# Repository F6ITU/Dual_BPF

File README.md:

# Alexiares dual BPF for Orion/Anvelina SDR Board

1 to 60 MHz Band pass filter for dual ADC SDR  (Orion class, Anvelina, Red Pitaya)

This pcb serves as RX bandpass for the new generation of Alexiares frontend

It replace the former Alexiares HPF filter and uses the very same SPI bus protocol

Please note that on BPF1  

K23, FB45, FB46, R11, R12, C106 and C93 should NOT be soldered

 (pads 3-10 and 9-4 should be strapped)
 
Signal RX2_GND is not used

BPF2 should be fully assembled, with K23, FB45, FB46, R11, R12, C106 and C93. Signal RX2_GND should be present on J6

(see Alexandrie V2 wirering )

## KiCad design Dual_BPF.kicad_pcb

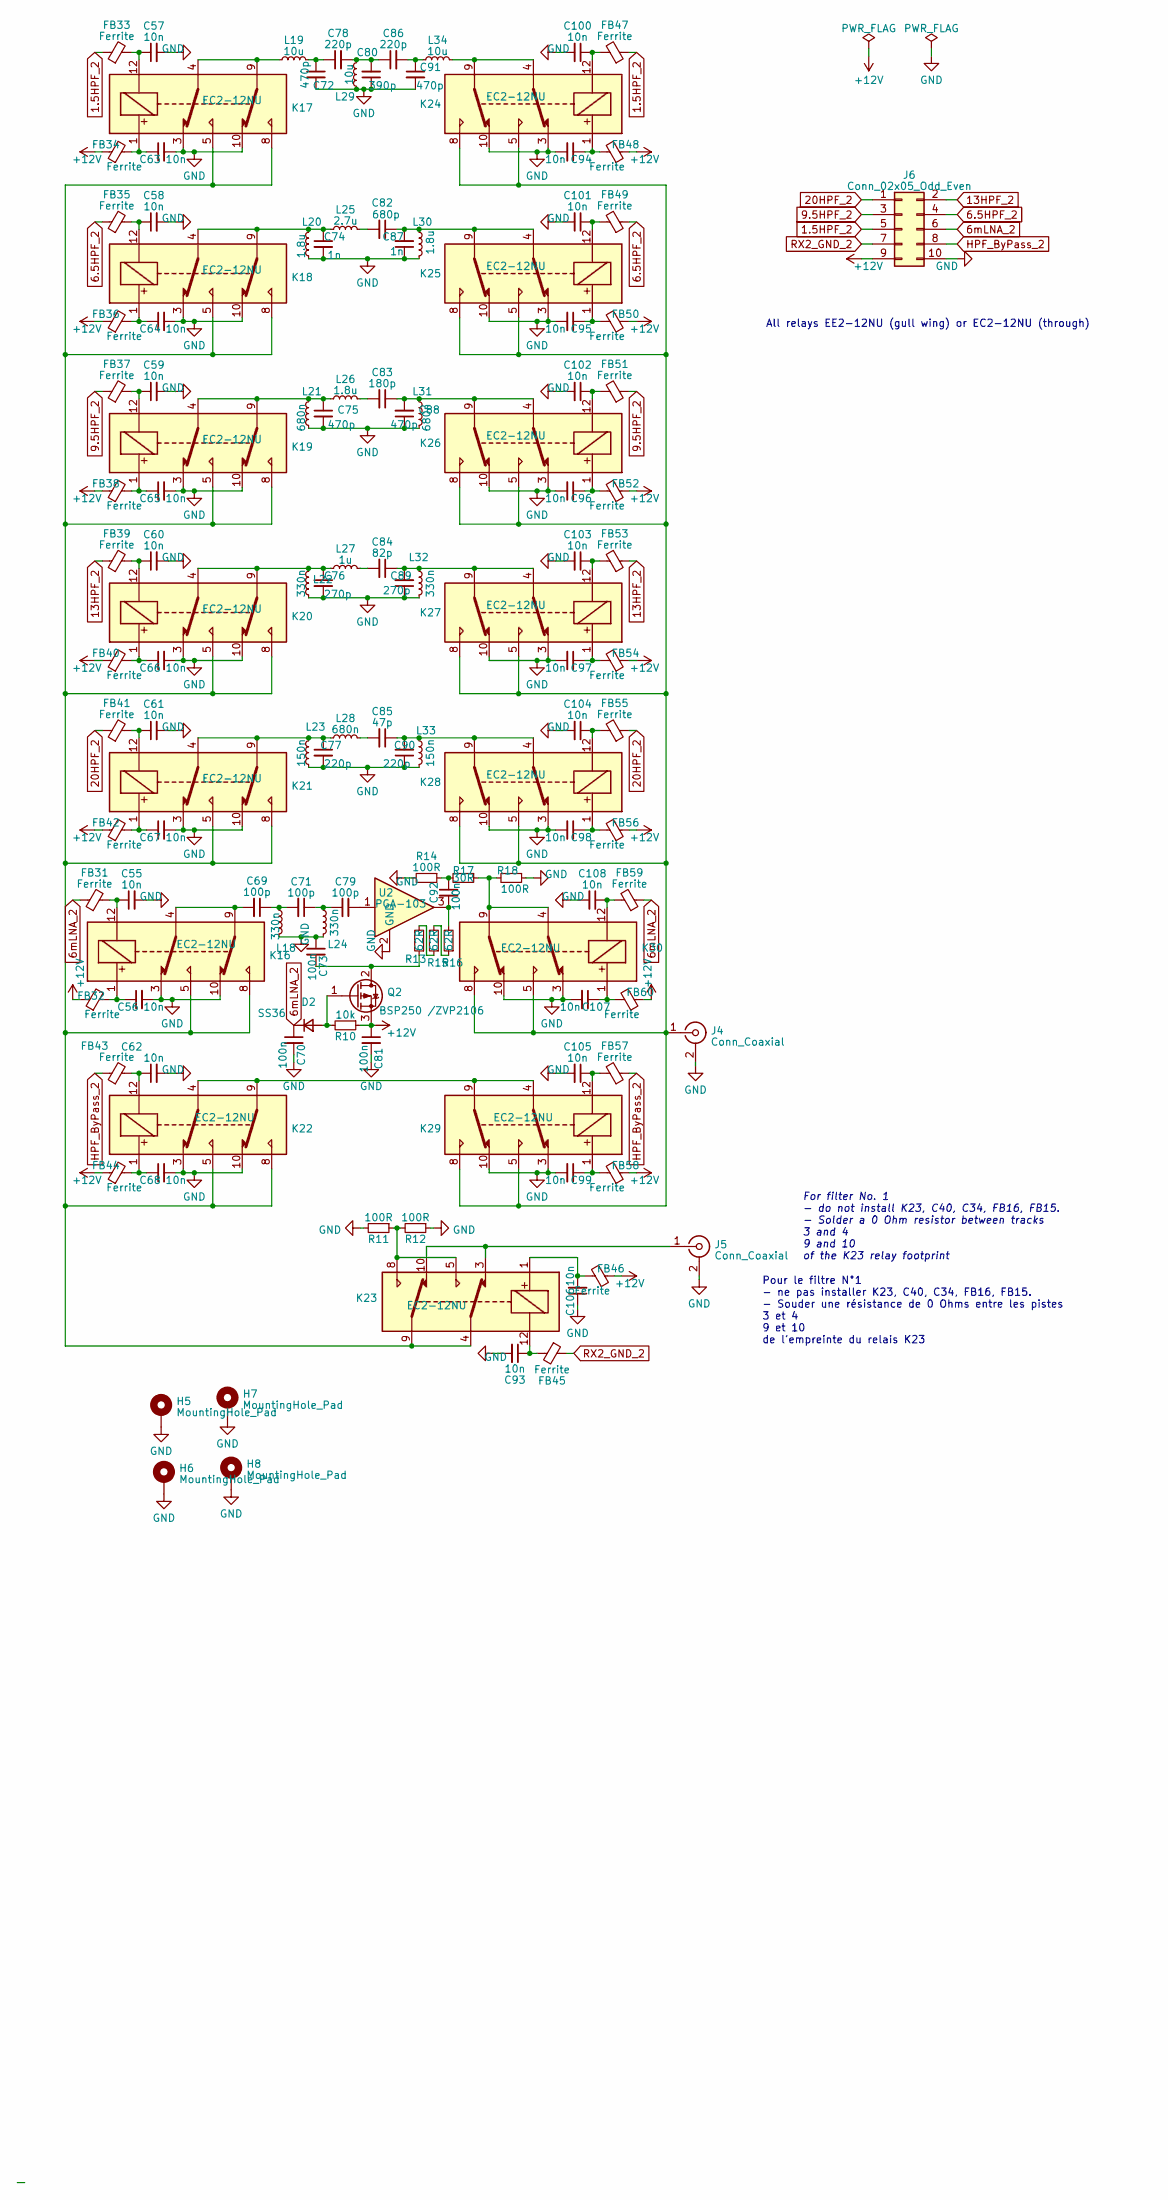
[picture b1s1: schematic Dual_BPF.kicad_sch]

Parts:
C55, C56, C57, C58, C59, C60, C61, C62, C63, C64, C65, C66, C67, C68, C93, C94, C95, C96, C97, C98, C99, C100, C101, C102, C103, C104, C105, C106, C107, C108: 10n; C_0805_2012Metric_Pad1.18x1.45mm_HandSolder
C69, C71, C79: 100p; C_0805_2012Metric_Pad1.18x1.45mm_HandSolder
C70, C73, C81, C92: 100n; C_0805_2012Metric_Pad1.18x1.45mm_HandSolder
C72, C75, C88, C91: 470p; C_0805_2012Metric_Pad1.18x1.45mm_HandSolder
C74, C87: 1n; C_0805_2012Metric_Pad1.18x1.45mm_HandSolder
C76, C89: 270p; C_0805_2012Metric_Pad1.18x1.45mm_HandSolder
C77, C78, C86, C90: 220p; C_0805_2012Metric_Pad1.18x1.45mm_HandSolder
C80: 390p; C_0805_2012Metric_Pad1.18x1.45mm_HandSolder
C82: 680p; C_0805_2012Metric_Pad1.18x1.45mm_HandSolder
C83: 180p; C_0805_2012Metric_Pad1.18x1.45mm_HandSolder
C84: 82p; C_0805_2012Metric_Pad1.18x1.45mm_HandSolder
C85: 47p; C_0805_2012Metric_Pad1.18x1.45mm_HandSolder
D2: SS36; D_SMB
FB31, FB32, FB33, FB34, FB35, FB36, FB37, FB38, FB39, FB40, FB41, FB42, FB43, FB44, FB45, FB46, FB47, FB48, FB49, FB50, FB51, FB52, FB53, FB54, FB55, FB56, FB57, FB58, FB59, FB60: Ferrite; L_0805_2012Metric
H5, H6, H7, H8: MountingHole_Pad; MountingHole_3.2mm_M3_ISO14580_Pad
J4, J5: Conn_Coaxial; SMA_PINS
J6: Conn_02x05_Odd_Even; IDC-Header_2x05_P2.54mm_Vertical
K16, K17, K18, K19, K20, K21, K22, K23, K24, K25, K26, K27, K28, K29, K30: EC2-12NU; Relay_DPDT_Kemet_EC2
L18, L22, L24, L32: 330n; L_1812_4532Metric_Pad1.30x3.40mm_HandSolder
L19, L29, L34: 10u; L_1812_4532Metric_Pad1.30x3.40mm_HandSolder
L20, L26, L30: 1.8u; L_1812_4532Metric_Pad1.30x3.40mm_HandSolder
L21, L28, L31: 680n; L_1812_4532Metric_Pad1.30x3.40mm_HandSolder
L23, L33: 150n; L_1812_4532Metric_Pad1.30x3.40mm_HandSolder
L25: 2.7u; L_1812_4532Metric_Pad1.30x3.40mm_HandSolder
L27: 1u; L_1812_4532Metric_Pad1.30x3.40mm_HandSolder
Q2: BSP250 /ZVP2106; SOT-223-3_TabPin2
R10: 10k; R_0805_2012Metric_Pad1.20x1.40mm_HandSolder
R11, R12, R14, R18: 100R; R_0805_2012Metric_Pad1.20x1.40mm_HandSolder
R13, R15, R16: 62R; R_0805_2012Metric_Pad1.20x1.40mm_HandSolder
R17: 30R; R_0805_2012Metric_Pad1.20x1.40mm_HandSolder
U2: PGA-103; SOT-89-3

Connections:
1.5HPF_2: FB33.1, FB47.1, J6.5
6.5HPF_2: FB35.1, FB49.1, J6.4
6mLNA_2: C70.1, D2.1 (K), FB31.1, FB59.1, J6.6
9.5HPF_2: FB37.1, FB51.1, J6.3
13HPF_2: FB39.1, FB53.1, J6.2
20HPF_2: FB41.1, FB55.1, J6.1
+12V: C81.1, FB32.1, FB34.1, FB36.1, FB38.1, FB40.1, FB42.1, FB44.1, FB46.1, FB48.1, FB50.1, FB52.1, FB54.1, FB56.1, FB58.1, FB60.1, J6.9, Q2.3 (S), R10.1
GND: C55.2, C56.2, C57.2, C58.2, C59.2, C60.2, C61.2, C62.2, C63.2, C64.2, C65.2, C66.2, C67.2, C68.2, C70.2, C72.2, C73.1, C74.2, C75.2, C76.2, C77.2, C80.1, C81.2, C87.1, C88.1, C89.1, C90.1, C91.2, C93.2, C94.2, C95.2, C96.2, C97.2, C98.2, C99.2, C100.2, C101.2, C102.2, C103.2, C104.2, C105.2, C106.1, C107.2, C108.2, H5.1, H6.1, H7.1, H8.1, J4.2 (Ext), J5.2 (Ext), J6.10, K16.3, K16.10, K17.3, K17.10, K18.3, K18.10, K19.3, K19.10, K20.3, K20.10, K21.3, K21.10, K22.3, K22.10, K24.3, K24.10, K25.3, K25.10, K26.3, K26.10, K27.3, K27.10, K28.3, K28.10, K29.3, K29.10, K30.3, K30.10, L18.2, L20.1, L21.1, L22.1, L23.1, L24.2, L29.2, L30.2, L31.2, L32.2, L33.2, R11.2, R12.1, R14.2, R18.1, U2.2 (GND)
HPF_ByPass_2: FB43.1, FB57.1, J6.8
unnamed: C55.1, FB31.2, K16.12
unnamed: C56.1, FB32.2, K16.1
unnamed: C57.1, FB33.2, K17.12
unnamed: C58.1, FB35.2, K18.12
unnamed: C59.1, FB37.2, K19.12
unnamed: C60.1, FB39.2, K20.12
unnamed: C61.1, FB41.2, K21.12
unnamed: C62.1, FB43.2, K22.12
unnamed: C63.1, FB34.2, K17.1
unnamed: C64.1, FB36.2, K18.1
unnamed: C65.1, FB38.2, K19.1
unnamed: C66.1, FB40.2, K20.1
unnamed: C67.1, FB42.2, K21.1
unnamed: C68.1, FB44.2, K22.1
unnamed: C69.1, C71.2, L18.1
unnamed: C69.2, K16.4, K16.9
unnamed: C71.1, C79.2, L24.1
unnamed: C72.1, C78.1, L19.1
unnamed: C74.1, K18.4, K18.9, L20.2, L25.1
unnamed: C75.1, K19.4, K19.9, L21.2, L26.1
unnamed: C76.1, K20.4, K20.9, L22.2, L27.1
unnamed: C77.1, K21.4, K21.9, L23.2, L28.1
unnamed: C78.2, C80.2, C86.1, L29.1
unnamed: C79.1, U2.1
unnamed: C82.1, C87.2, K25.4, K25.9, L30.1
unnamed: C82.2, L25.2
unnamed: C83.1, C88.2, K26.4, K26.9, L31.1
unnamed: C83.2, L26.2
unnamed: C84.1, C89.2, K27.4, K27.9, L32.1
unnamed: C84.2, L27.2
unnamed: C85.1, C90.2, K28.4, K28.9, L33.1
unnamed: C85.2, L28.2
unnamed: C86.2, C91.1, L34.2
unnamed: C92.1, R14.1, R17.2
unnamed: C92.2, R16.2, U2.3
unnamed: C93.1, FB45.2, K23.12
unnamed: C94.1, FB48.2, K24.1
unnamed: C95.1, FB50.2, K25.1
unnamed: C96.1, FB52.2, K26.1
unnamed: C97.1, FB54.2, K27.1
unnamed: C98.1, FB56.2, K28.1
unnamed: C99.1, FB58.2, K29.1
unnamed: C100.1, FB47.2, K24.12
unnamed: C101.1, FB49.2, K25.12
unnamed: C102.1, FB51.2, K26.12
unnamed: C103.1, FB53.2, K27.12
unnamed: C104.1, FB55.2, K28.12
unnamed: C105.1, FB57.2, K29.12
unnamed: C106.2, FB46.2, K23.1
unnamed: C107.1, FB60.2, K30.1
unnamed: C108.1, FB59.2, K30.12
unnamed: D2.2 (A), Q2.1 (G), R10.2
unnamed: J4.1 (In), K24.5, K24.8, K25.5, K25.8, K26.5, K26.8, K27.5, K27.8, K28.5, K28.8, K29.5, K29.8, K30.5, K30.8
unnamed: J5.1 (In), K23.3, K23.10
unnamed: K16.5, K16.8, K17.5, K17.8, K18.5, K18.8, K19.5, K19.8, K20.5, K20.8, K21.5, K21.8, K22.5, K22.8, K23.4, K23.9
unnamed: K17.4, K17.9, L19.2
unnamed: K22.4, K22.9, K29.4, K29.9
unnamed: K23.5, K23.8, R11.1, R12.2
unnamed: K24.4, K24.9, L34.1
unnamed: K30.4, K30.9, R17.1, R18.2
unnamed: C73.2, Q2.2 (D), R13.1
unnamed: R13.2, R15.1
unnamed: R15.2, R16.1
RX2_GND_2: FB45.1, J6.7

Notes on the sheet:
Pour le filtre N°1 - ne pas installer K23, C40, C34, FB16, FB15. - Souder une résistance de 0 Ohms entre les pistes 3 et 4 9 et 10 de l'empreinte du relais K23
All relays EE2-12NU (gull wing) or EC2-12NU (through)
For filter No. 1 - do not install K23, C40, C34, FB16, FB15. - Solder a 0 Ohm resistor between tracks 3 and 4 9 and 10 of the K23 relay footprint

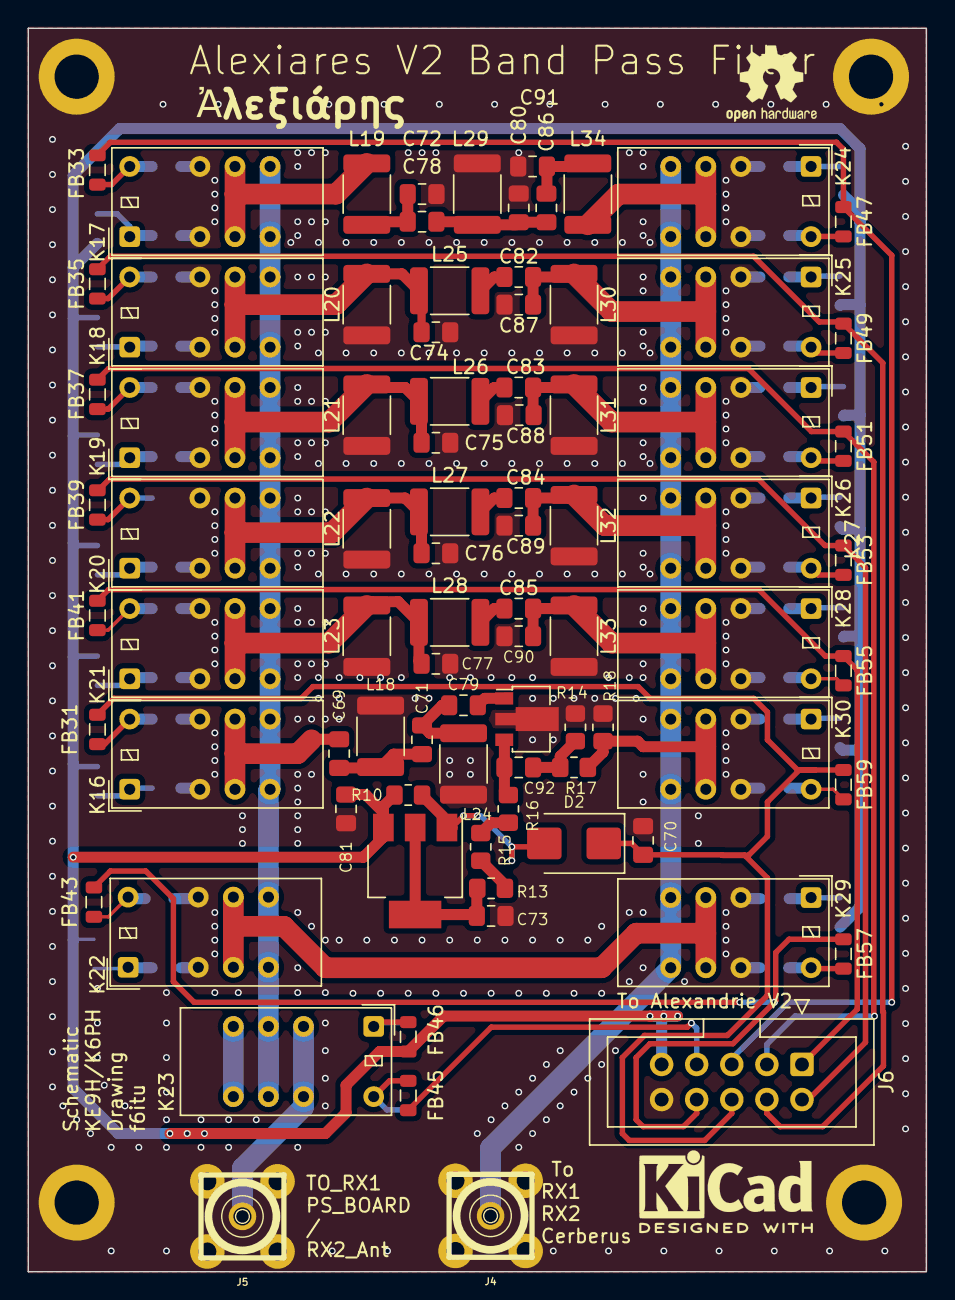
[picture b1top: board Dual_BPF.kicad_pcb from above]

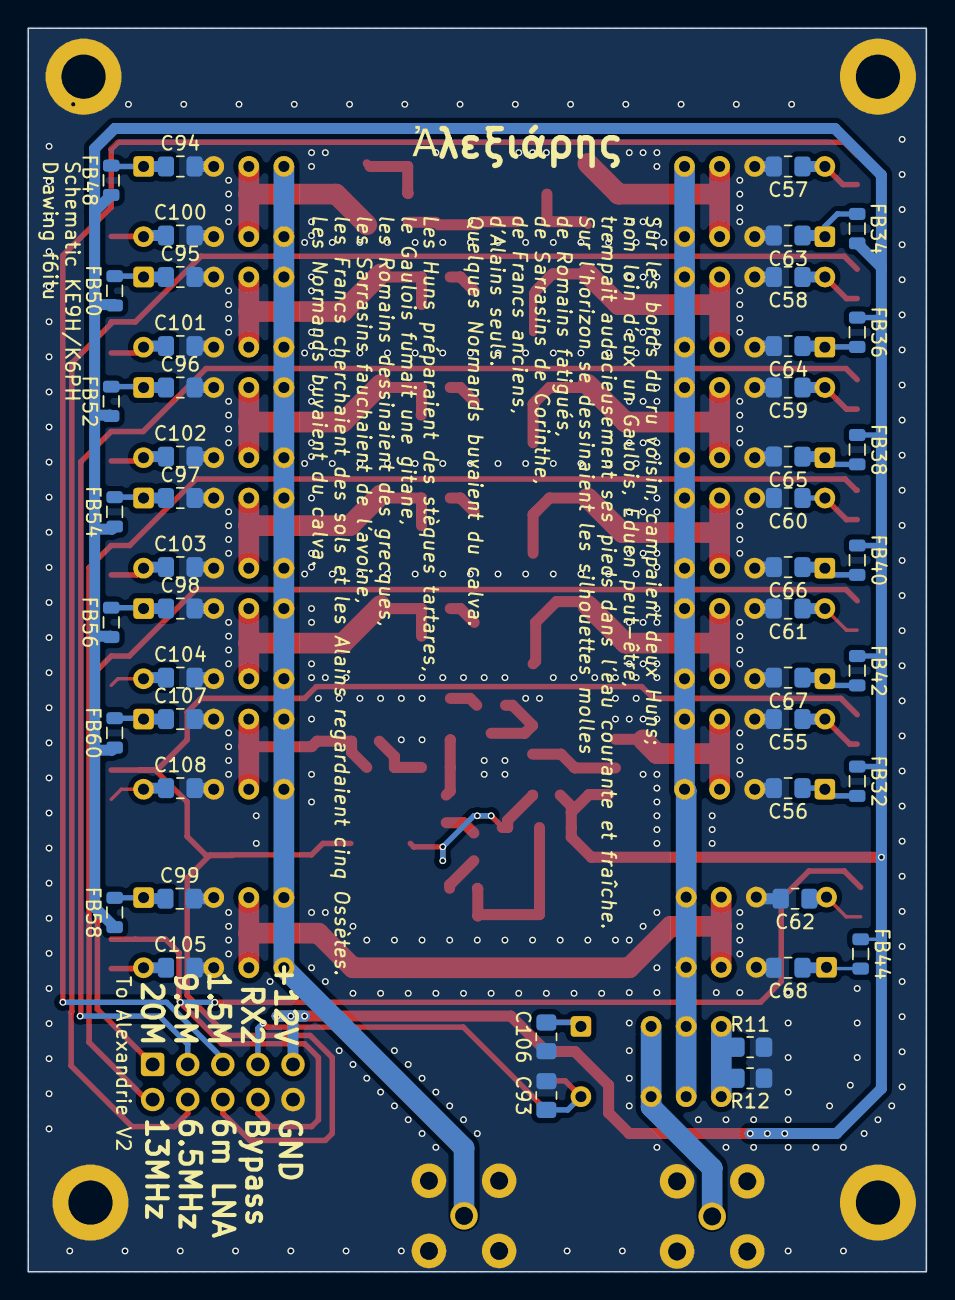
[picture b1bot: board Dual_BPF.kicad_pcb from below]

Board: 2 copper layers, 65.0 x 90.0 mm, 135 parts (46 on the bottom side), 73 nets.

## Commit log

2023-04-13 first commit, schematic partially designed
2023-04-16 work in progress, 2 different pcb
2023-04-17 SMD version RTM 1.0, toroid version deleted
2023-04-17 silk done
2023-04-17 picture, iBom, BOM, pdf Schematic added
2023-04-17 new readme
2023-04-18 Elsie simulations added
2023-04-19 added an S2P directory with simulation datas
2023-05-03 fix some silkscreen errors, new gerber
2023-05-11 new schematic pdf file, thank you, Sigi
2023-05-12 small mods on schematic comments
2024-12-11 minor changes and new iBom
2026-04-24 pictures and wiki added
2026-04-24 kicad 10 updated, wiki added
